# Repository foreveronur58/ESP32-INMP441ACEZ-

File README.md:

# HONUR.SOLO Mic Board

A custom 2-layer PCB built around the ESP32-S3-MINI-N8 module, with an INMP441
I2S MEMS microphone, powered over USB-B. Designed in KiCad.

## Features
- ESP32-S3-MINI-1-N8 (WiFi + BLE + native USB)
- INMP441 I2S digital microphone
- AMS1117-3.3 regulator (5V VBUS -> 3.3V)
- Mini USB-B connector
- EN and BOOT buttons, status LED
- Board size: XX x XX mm, 2 layers, 1.6 mm

## Repository Contents
- `*.kicad_sch`, `*.kicad_pcb`: schematic and PCB layout

## Design Notes
- GND copper pour on B.Cu; the ESP32 thermal pad is stitched to it with vias
- No copper or vias under the ESP32 antenna area (keepout respected)
- All footprints were checked against manufacturer land patterns
- The INMP441 footprint from SnapMagic had an acoustic port hole of
  0.75 mm instead of the 0.25 mm in the datasheet, which caused a hole
  clearance DRC violation. Fixed by correcting the hole diameter
  (0.3 mm to stay within JLCPCB's minimum drill size).
- Net classes configured for JLCPCB's standard 2-layer capabilities

## Status
- [x] Schematic
- [x] PCB placement and routing
- [x] DRC clean
- [ ] Fabrication (JLCPCB PCBA)
- [ ] Hardware bring-up and testing

## License
All rights reserved.

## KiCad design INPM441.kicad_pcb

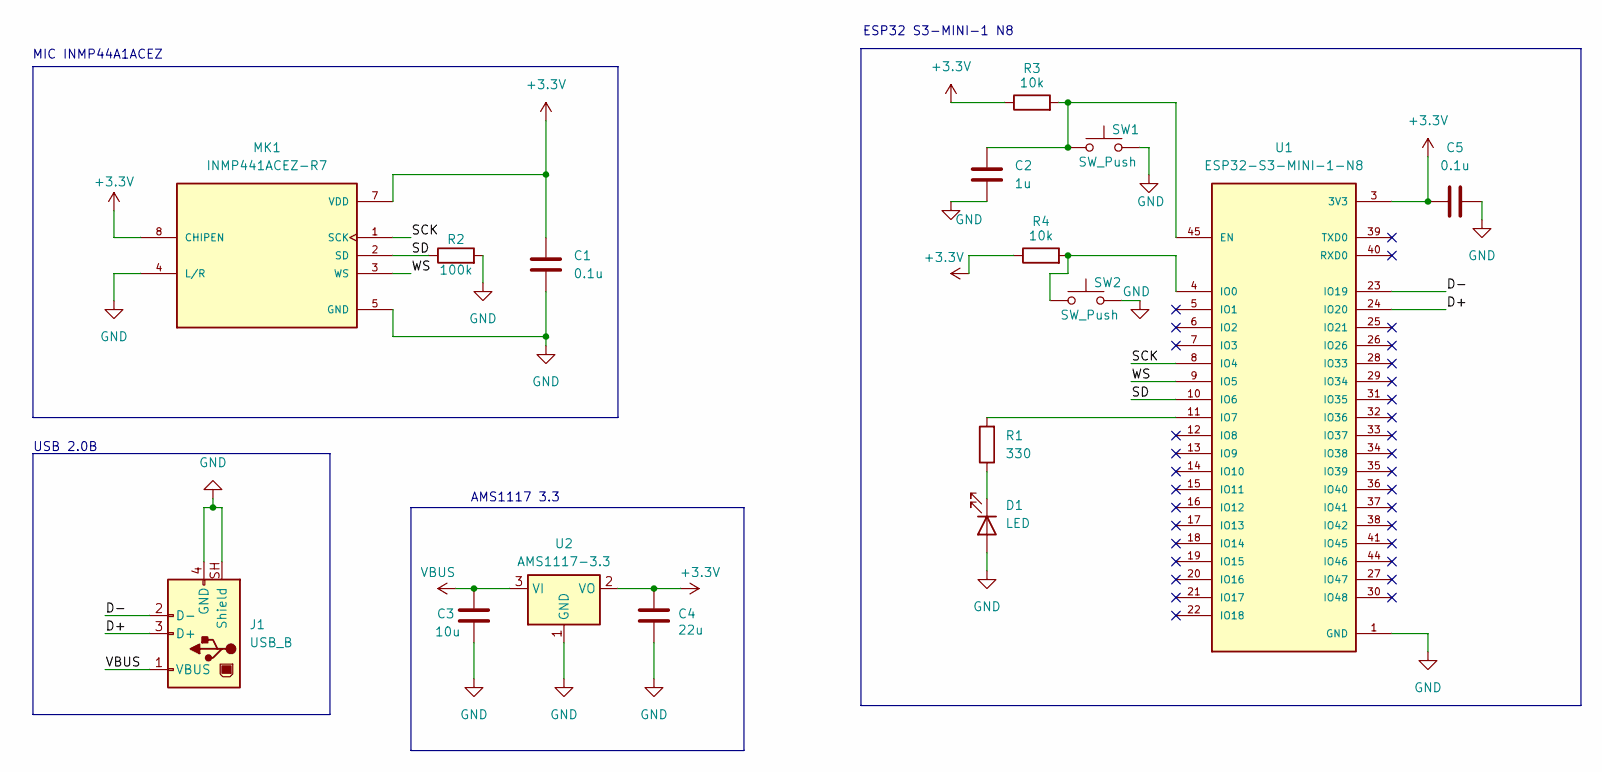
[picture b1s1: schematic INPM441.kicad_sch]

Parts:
C1, C5: 0.1u; C_0603_1608Metric
C2: 1u; C_0603_1608Metric
C3: 10u; CAPMP3216X180N
C4: 22u; CAPC3216X110N
D1: LED; LED_Cree-XHP50_3V_HighDensity
J1: USB_B; USB_Mini-B_Lumberg_2486_01_Horizontal
MK1: INMP441ACEZ-R7; MIC_INMP441ACEZ-R7; PARTREV 1.1
R1: 330; R_0603_1608Metric
R2: 100k; R_0603_1608Metric
R3, R4: 10k; R_0603_1608Metric
SW1, SW2: SW_Push; B3U-1000P
U1: ESP32-S3-MINI-1-N8; XCVR_ESP32-S3-MINI-1-N8; PARTREV v0.6
U2: AMS1117-3.3; SOT229P700X180-4N

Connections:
+3.3V: C1.1, C4.1, C5.1, MK1.7 (VDD), MK1.8 (CHIPEN), R3.1, R4.1, U1.3 (3V3), U2.2 (VO)
/D+: J1.3 (D+), U1.24 (IO20)
/D-: J1.2 (D-), U1.23 (IO19)
/SCK: MK1.1 (SCK), U1.8 (IO4)
/SD: MK1.2 (SD), R2.1, U1.10 (IO6)
/WS: MK1.3 (WS), U1.9 (IO5)
GND: C1.2, C2.2, C3.2, C4.2, C5.2, D1.2 (A), J1.4 (GND), J1.SH (Shield), MK1.4 (L/R), MK1.5 (GND), MK1.6 (GND), MK1.9 (GND), R2.2, SW1.2, SW2.2, U1.1 (GND), U1.2 (GND), U1.42 (GND), U1.43 (GND), U1.46 (GND), U1.47 (GND), U1.48 (GND), U1.49 (GND), U1.50 (GND), U1.51 (GND), U1.52 (GND), U1.53 (GND), U1.54 (GND), U1.55 (GND), U1.56 (GND), U1.57 (GND), U1.58 (GND), U1.59 (GND), U1.60 (GND), U1.61 (GND), U1.61_1 (GND), U1.61_2 (GND), U1.61_3 (GND), U1.61_4 (GND), U1.61_5 (GND), U1.61_6 (GND), U1.61_7 (GND), U1.61_8 (GND), U1.62 (GND), U1.63 (GND), U1.64 (GND), U1.65 (GND), U2.1 (GND)
unnamed: D1.1 (K), R1.1
unnamed: C2.1, R3.2, SW1.1, U1.45 (EN)
unnamed: R4.2, SW2.1, U1.4 (IO0)
unnamed: R1.2, U1.11 (IO7)
VBUS: C3.1, J1.1 (VBUS), U2.3 (VI)

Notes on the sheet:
USB 2.0B
AMS1117 3.3
ESP32 S3-MINI-1 N8
MIC INMP44A1ACEZ

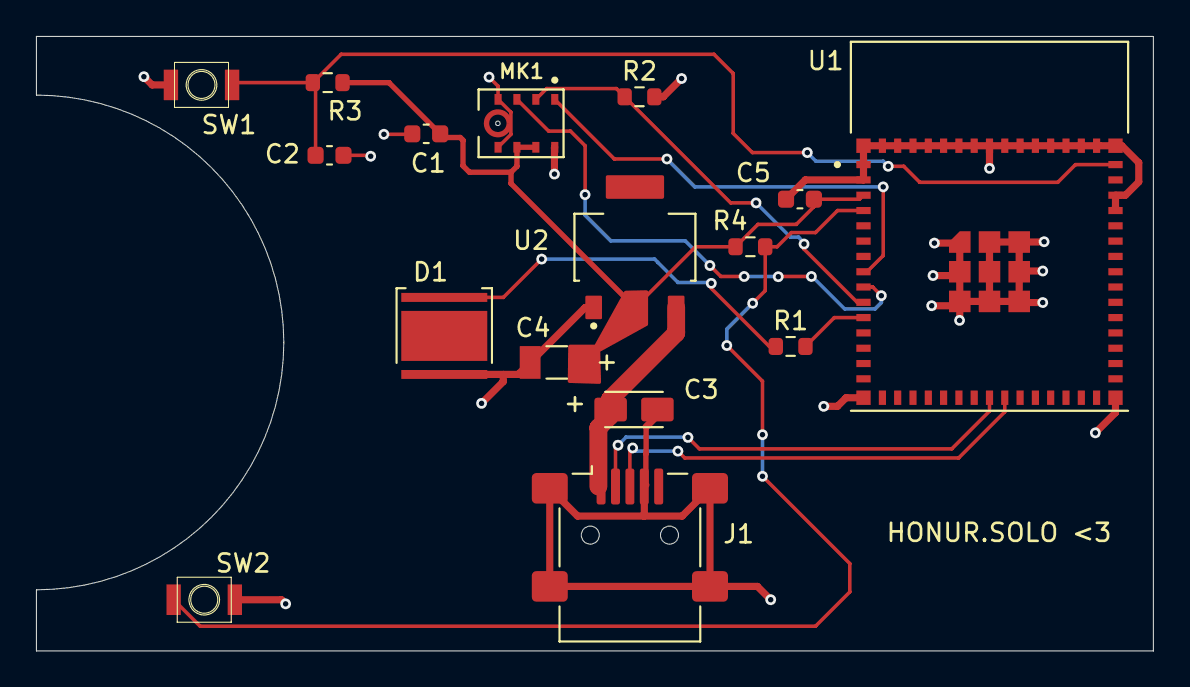
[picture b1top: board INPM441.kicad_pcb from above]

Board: 2 copper layers, 62.1 x 34.1 mm, 16 parts (0 on the bottom side), 12 nets.
